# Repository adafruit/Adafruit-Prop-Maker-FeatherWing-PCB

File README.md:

## Adafruit Prop-Maker FeatherWing PCB

<a href="http://www.adafruit.com/products/3988"><br/>
Click here to purchase one from the Adafruit shop</a>

PCB files for the Adafruit Prop-Maker FeatherWing. Format is EagleCAD schematic and board layout
* https://www.adafruit.com/product/3988

### Description

The Adafruit Feather series gives you lots of options for a small, portable, rechargeable microcontroller board. Perfect for fitting into your next prop build! This FeatherWing will unlock the prop-maker inside all of us, with tons of stuff packed in to make sabers & swords, props, toys, cosplay pieces, and more.

We looked at hundreds of prop builds, and thought about what would make for a great low-cost (but well-designed) add-on for our Feather boards. Here's what we came up with:

 * **Snap-in NeoPixel port** - With a 3-pin JST connector, you can [plug in one of our JST-wired NeoPixel strips directly](https://www.adafruit.com/product/3919), or use a [3-pin JST connector to wire up your favorite shape of addressable NeoPixel LEDs](https://www.adafruit.com/?q=jst%203-pin). This port provides high current drive from either the Feather Lipoly or USB port, whichever is higher. A level shifter gives you a clean voltage signal to reduce glitchiness no matter what chip you're using
 * **3W RGB LED drivers** - 3 high current MOSFETs will let you [connect a 3W RGB LED for powerful eye-blasting glory](https://www.adafruit.com/product/2530). For most Feathers, the 3 pins are PWM capable so you can generate any color you like. Available as pin breakouts plus strain-relief holes
 * **Triple-Axis Accelerometer with Tap Detection** - The LIS3DH is our favorite accelerometer, you can use this for detection motion, tilt or taps. [Here's an example of a light saber that makes sounds when swung or hit](https://learn.adafruit.com/hallowing-lightsaber). We have code for this chip in both Arduino and CircuitPython.
 * **Class D Audio Amplifier** - Drive a 8Ω 1Watt speaker or 4Ω 3W speaker for sound effects. [Plug and play with our cute and slim oval speaker](https://www.adafruit.com/product/3923), or [connect a picoblade cable](https://www.adafruit.com/product/3922) for your favorite speaker. For use only with Feathers that have analog audio out such as the Feather M0 Express and M4 series.
 * **Low power mode!** The power system for the RGB LED, NeoPixels and speaker amplifier can be controlled by a pin to cut power to them, so you have lower power usage when the prop is in sleep or off mode (but can wake up fast by listening to the button press or accelerometer data). When the power pin is set low, the current draw for just the wing is under 1mA and no there's current draw from any attached NeoPixels - normally they're about 1mA even when not lit.
 * Breakouts plus strain-relief hole for the enable pin and ground (for a mechanical switch that will power down the whole board)
 * Breakouts plus strain-relief holes for an external switch pin and ground (for a mechanical mode button)
**Please note**: A few of the onboard hardware elements use PWM and analog output so we recommend the **Feather M0 Express or Feather M4** series, they'll work best with this wing and let you make the most of it. For example:

Feather 32u4 and 328p do not have PWMs for all the RGB LED pins, and no analog audio output support
Feather nRF52, ESP32 ESP8266 do have PWMs on all the RGB LED pins but no analog audio output support
Feather M0 basic boards only have audio output support in Arduino, not CircuitPython.
That doesn't mean you can't use this 'wing with the Feather ESP8266 or nRF52832, just that you won't get any sound effects. You can still use the accelerometer, NeoPixels, RGB LED, etc.

As you can tell, the **M0 Express and M4** series is what we recommend cause you'll get everything and with CircuitPython, its really easy to play audio directly off the built in flash chips!

### License

Adafruit invests time and resources providing this open source design, please support Adafruit and open-source hardware by purchasing products from [Adafruit](https://www.adafruit.com)!

Designed by Limor Fried/Ladyada for Adafruit Industries.

Creative Commons Attribution/Share-Alike, all text above must be included in any redistribution. See license.txt for additional details.

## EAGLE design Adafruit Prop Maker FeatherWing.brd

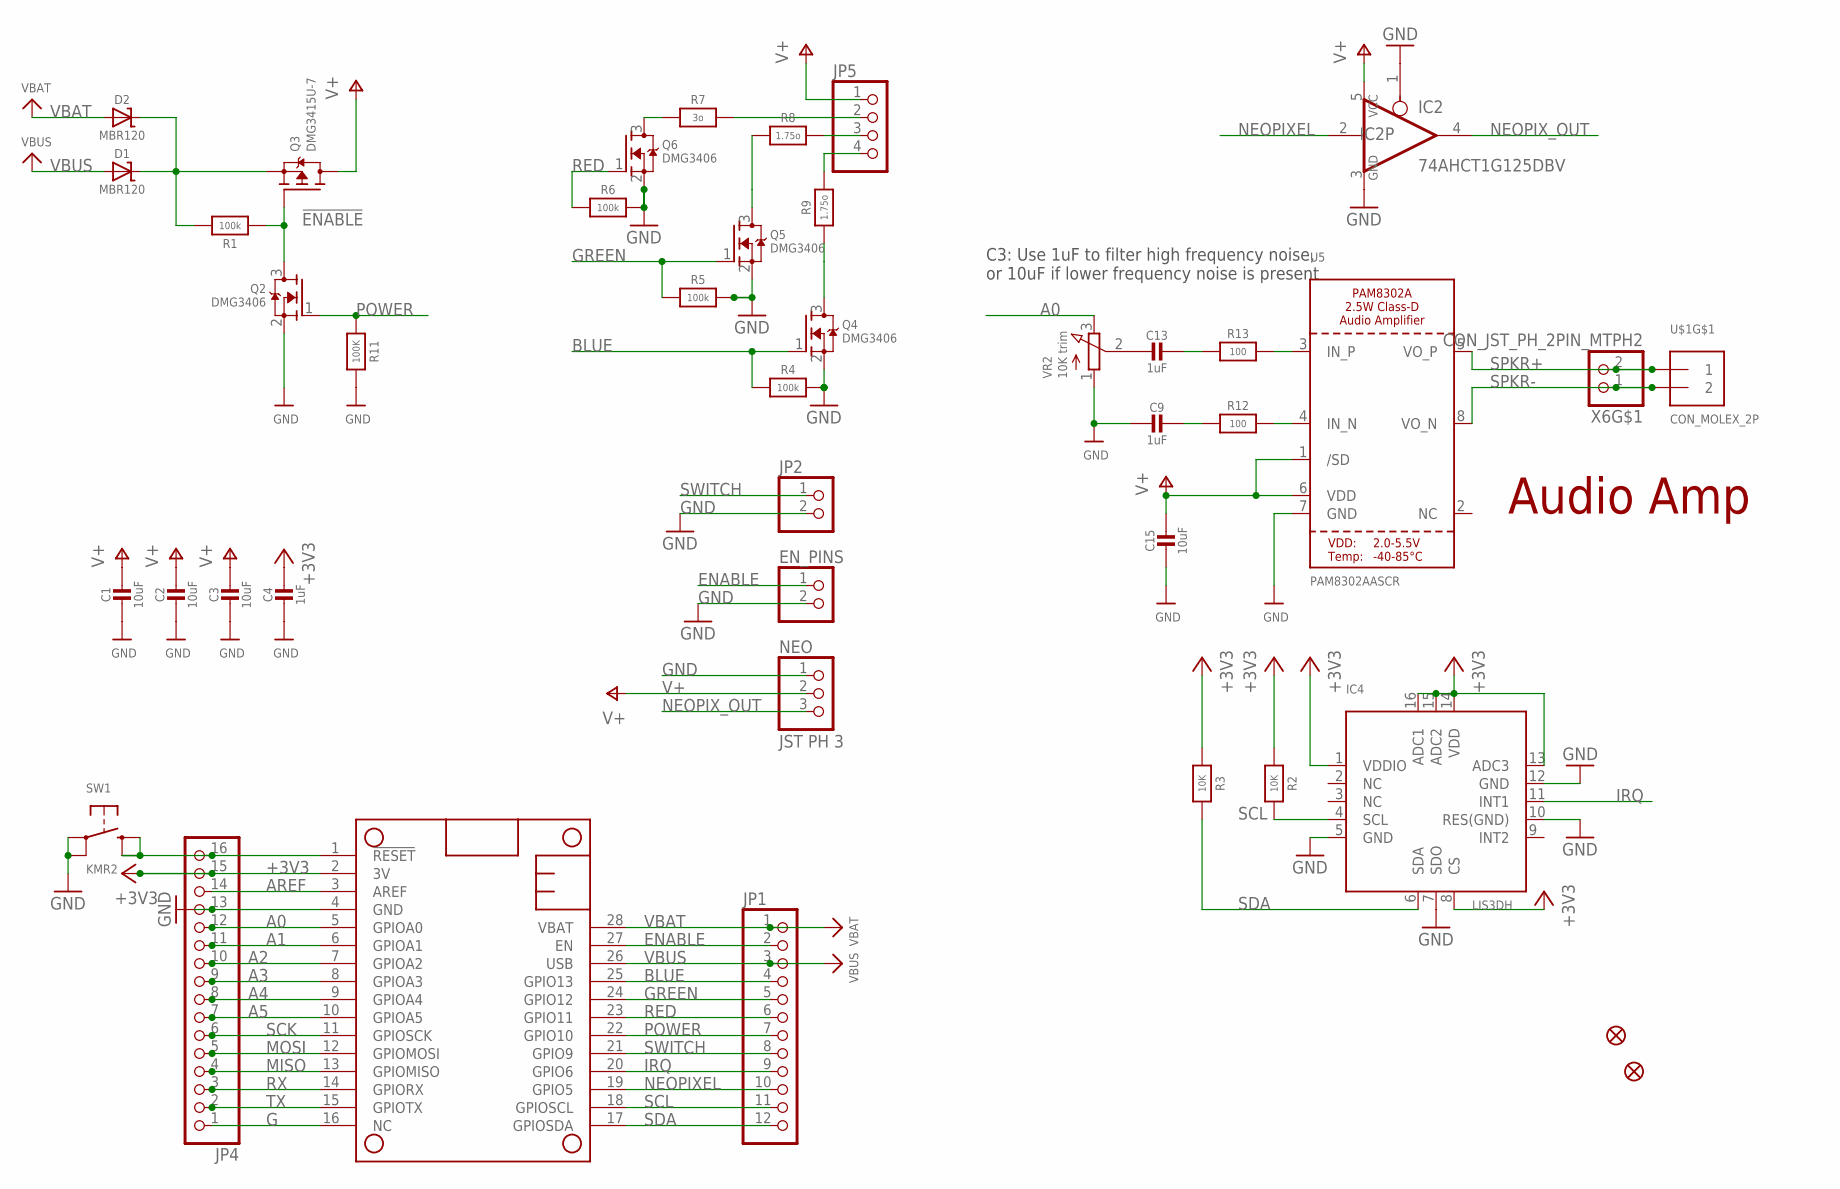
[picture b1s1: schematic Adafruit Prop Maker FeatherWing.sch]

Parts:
C1, C2, C3, C15: 10uF; 0805-NO
C4, C9, C13: 1uF; 0603-NO
D1, D2: MBR120; SOD-123
EN_PINS: HEADER-1X2ROUND; 1X02_ROUND
FID1, FID3: FIDUCIAL_1MM
IC2: 74AHCT1G125DBV; SOT23-5
IC4: LIS3DH; LGA16_3X3MM
JP1: HEADER-1X12; 1X12_ROUND
JP2: HEADER-1X2ROUND; 1X02_ROUND
JP4: HEADER-1X16ROUND; 1X16_ROUND
JP5: HEADER-1X4ROUND; 1X04_ROUND
MS1: FEATHERWING
NEO: JST PH 3; JSTPH3
Q2, Q4, Q5, Q6: DMG3406; SOT23-WIDE
Q3: DMG3415U-7; SOT23-WIDE
R1, R4, R5, R6: 100k; 0603-NO
R2, R3: 10K; 0603-NO
R7: 3o; _1206
R8, R9: 1.75o; _1206
R11: 100K; 0603-NO
R12, R13: 100; 0603-NO
SW1: KMR2; BTN_KMR2_4.6X2.8
U5: PAM8302AASCR; MSOP8_0.65MM
U$1: CON_MOLEX_2P; 53398-0271
VR2: 10K trim; TRIMPOT_BOURNS_3303W
X6: CON_JST_PH_2PIN_MTPH2; JSTPH2

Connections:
!ENABLE: Q2.3 (D), Q3.1 (G), R1.1
+3V3: C4.1, IC4.1 (VDDIO), IC4.8 (CS), IC4.13 (ADC3), IC4.14 (VDD), IC4.15 (ADC2), IC4.16 (ADC1), JP4.15, MS1.2 (3V), R2.1, R3.1
A0: JP4.12, MS1.5 (GPIOA0), VR2.3 (E)
A1: JP4.11, MS1.6 (GPIOA1)
A2: JP4.10, MS1.7 (GPIOA2)
A3: JP4.9, MS1.8 (GPIOA3)
A4: JP4.8, MS1.9 (GPIOA4)
A5: JP4.7, MS1.10 (GPIOA5)
AREF: JP4.14, MS1.3 (AREF)
BLUE: JP1.4, MS1.25 (GPIO13), Q4.1 (G), R4.1
ENABLE: EN_PINS.1, JP1.2, MS1.27 (EN)
G: JP4.1, MS1.16 (NC)
GND: C1.2, C2.2, C3.2, C4.2, C9.2, C15.2, EN_PINS.2, IC2.1 (OE), IC2.3 (GND), IC4.5 (GND), IC4.7 (SDO), IC4.10 (RES(GND)), IC4.12 (GND), JP2.2, JP4.13, MS1.4 (GND), NEO.1, Q2.2 (S), Q4.2 (S), Q5.2 (S), Q6.2 (S), R4.2, R5.2, R6.2, R11.2, SW1.A, SW1.A' (P1), U5.7 (GND), VR2.1 (A)
GREEN: JP1.5, MS1.24 (GPIO12), Q5.1 (G), R5.1
IRQ: IC4.11 (INT1), JP1.9, MS1.20 (GPIO6)
MISO: JP4.4, MS1.13 (GPIOMISO)
MOSI: JP4.5, MS1.12 (GPIOMOSI)
unnamed: Q6.3 (D), R7.1
unnamed: JP5.3, R8.2
unnamed: JP5.4, R9.2
unnamed: Q4.3 (D), R9.1
unnamed: Q5.3 (D), R8.1
unnamed: JP5.2, R7.2
unnamed: R12.2, U5.4 (IN_N)
unnamed: R13.2, U5.3 (IN_P)
unnamed: C9.1, R12.1
unnamed: C13.1, R13.1
unnamed: C13.2, VR2.2 (S)
unnamed: D1.C, D2.C, Q3.2 (S), R1.2
NEOPIXEL: IC2.2 (I), JP1.10, MS1.19 (GPIO5)
NEOPIX_OUT: IC2.4 (O), NEO.3
POWER: JP1.7, MS1.22 (GPIO10), Q2.1 (G), R11.1
RED: JP1.6, MS1.23 (GPIO11), Q6.1 (G), R6.1
RESET: JP4.16, MS1.1 (!RESET), SW1.B (S), SW1.B' (S1)
RX: JP4.3, MS1.14 (GPIORX)
SCK: JP4.6, MS1.11 (GPIOSCK)
SCL: IC4.4 (SCL), JP1.11, MS1.18 (GPIOSCL), R2.2
SDA: IC4.6 (SDA), JP1.12, MS1.17 (GPIOSDA), R3.2
SPKR+: U5.5 (VO_P), U$1.1, X6.2
SPKR-: U5.8 (VO_N), U$1.2, X6.1
SWITCH: JP1.8, JP2.1, MS1.21 (GPIO9)
TX: JP4.2, MS1.15 (GPIOTX)
V+: C1.1, C2.1, C3.1, C15.1, IC2.5 (VCC), JP5.1, NEO.2, Q3.3 (D), U5.1 (/SD), U5.6 (VDD)
VBAT: D2.A, JP1.1, MS1.28 (VBAT)
VBUS: D1.A, JP1.3, MS1.26 (USB)

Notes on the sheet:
C3: Use 1uF to filter high frequency noise, or 10uF if lower frequency noise is present
Audio Amp

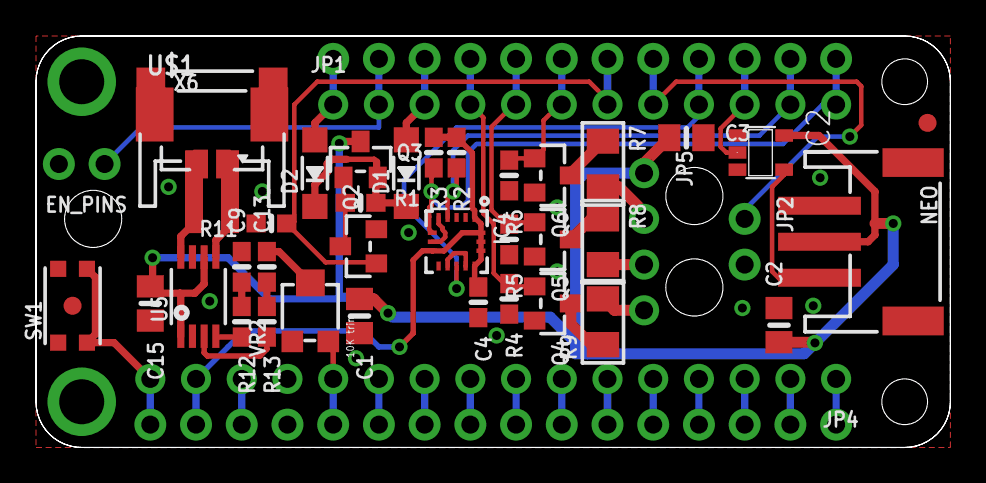
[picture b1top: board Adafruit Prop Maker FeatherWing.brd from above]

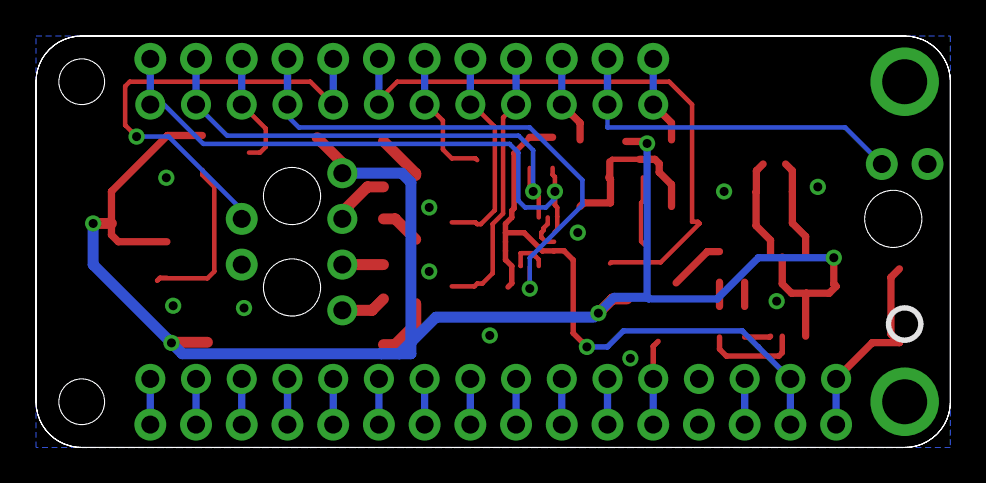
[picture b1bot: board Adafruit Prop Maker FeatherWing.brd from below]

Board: 2 copper layers, 50.8 x 22.9 mm, 45 parts (2 on the bottom side), 45 nets.

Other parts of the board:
U$6: PROPMAKER_BOT
U$14: PROPMAKER_TOP
U$15: PCBFEAT-REV-040

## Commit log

2018-11-03 init!
2019-07-16 update to use new pcb repo cookiecutter
